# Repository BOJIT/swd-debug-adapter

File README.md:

# swd-debug-adapter

Simple PCB to breakout various debug interfaces used across projects

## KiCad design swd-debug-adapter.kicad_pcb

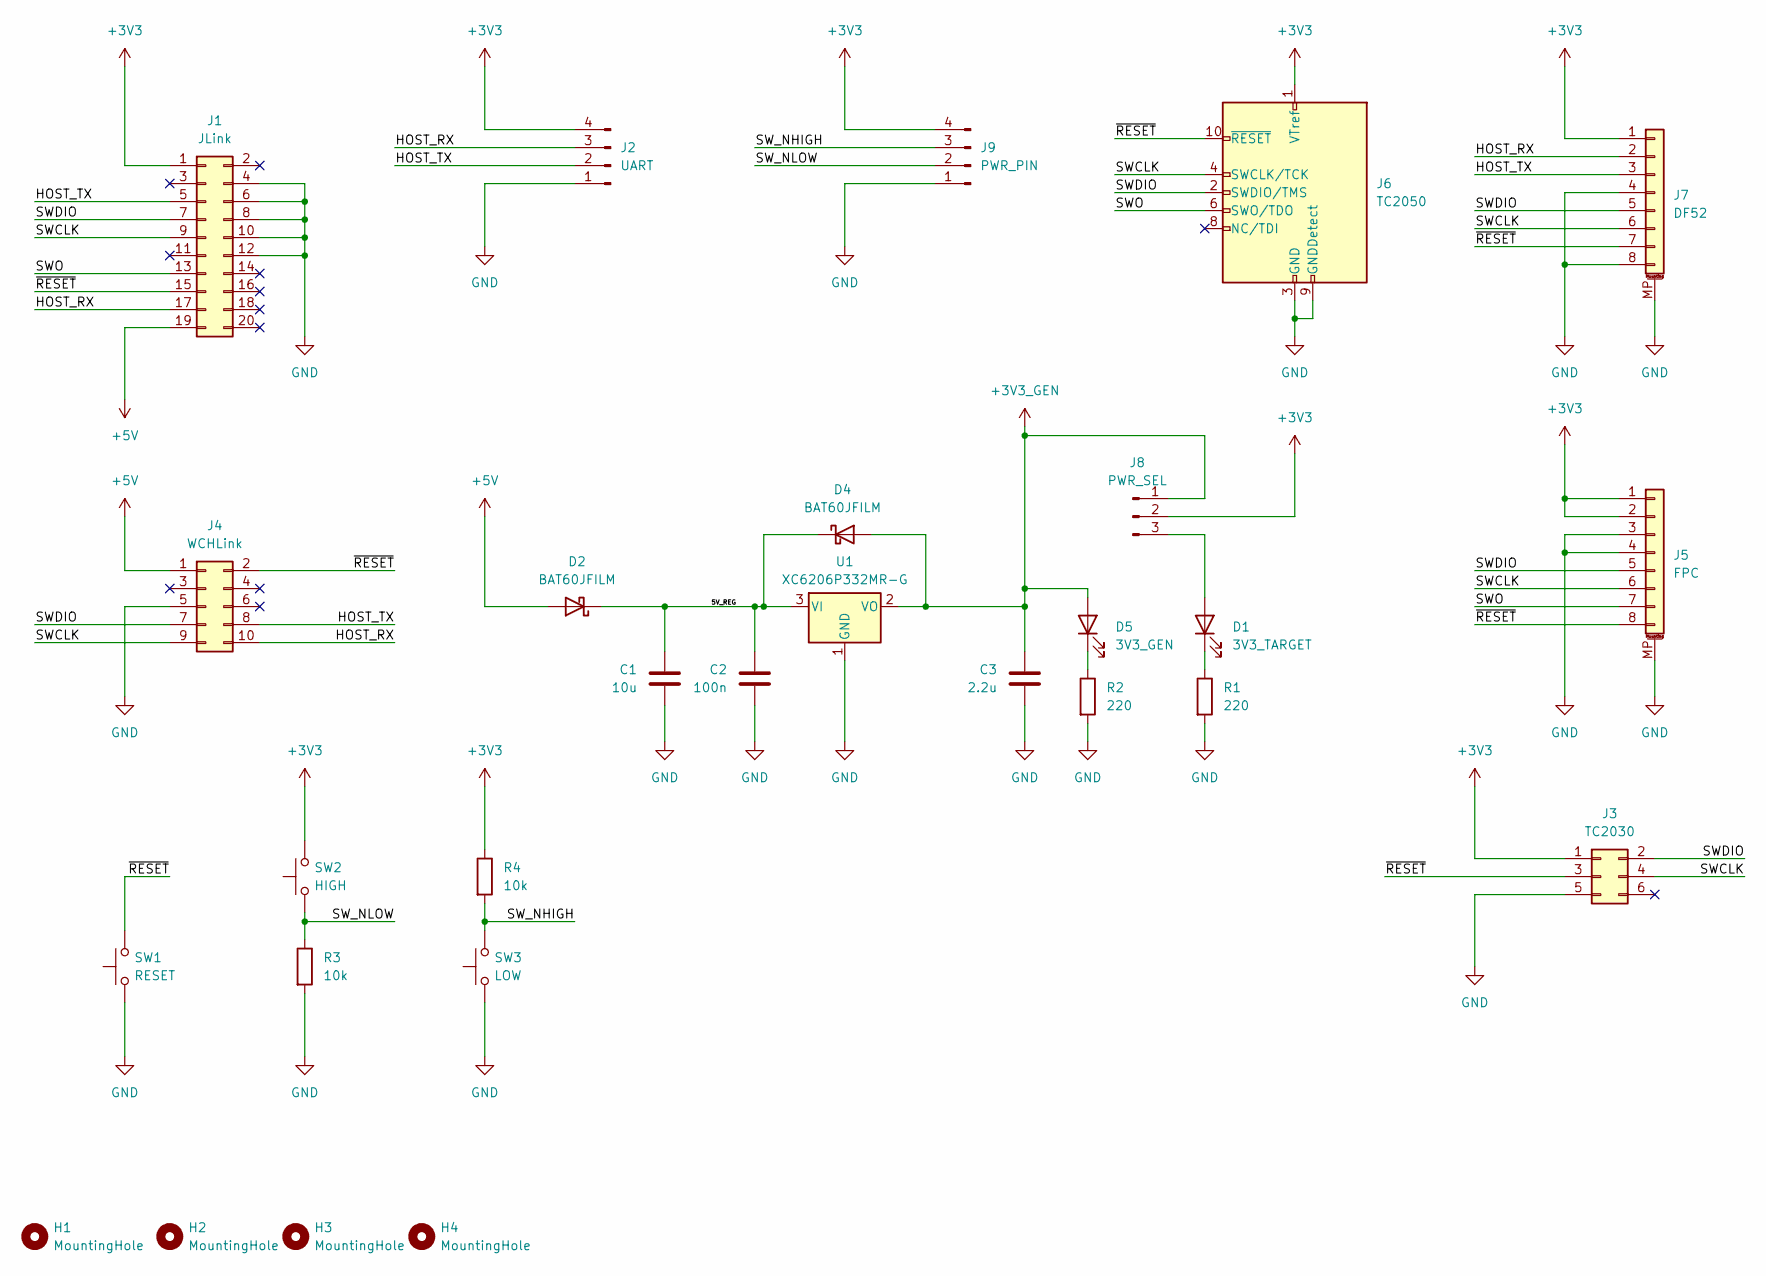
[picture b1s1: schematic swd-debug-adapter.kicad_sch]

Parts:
C1: 10u; C_0603_1608Metric; LCSC Part C19702
C2: 100n; C_0402_1005Metric; LCSC Part C1525
C3: 2.2u; C_0402_1005Metric; LCSC Part C12530
D1: 3V3_TARGET; LED_0603_1608Metric; LCSC Part C2286
D2, D4: BAT60JFILM; D_SOD-323; LCSC Part C133103
D5: 3V3_GEN; LED_0603_1608Metric; LCSC Part C2286
H1, H2, H3, H4: MountingHole; MountingHole_3.2mm_M3_Pad
J1: JLink; IDC-Header_2x10_P2.54mm_Vertical; LCSC Part C3405
J2: UART; PinHeader_1x04_P2.54mm_Vertical
J3: TC2030; CONN-TH_6P-P1.27_HX-JN1.27-2X3P-ZZ-H4.9; LCSC Part C42372545
J4: WCHLink; IDC-Header_2x05_P2.54mm_Vertical; LCSC Part C5665
J5: FPC; Hirose_FH12-8S-0.5SH_1x08-1MP_P0.50mm_Horizontal; LCSC Part C66953
J6: TC2050; CONN-TH_10P-P1.27_HX-JN1.27-2X5P-ZZ-H4.9; LCSC Part C42372547
J7: DF52; Hirose_DF52-8S-0.8H_1x08-1MP_P0.80mm_Horizontal; LCSC Part C506726
J8: PWR_SEL; PinHeader_1x03_P2.54mm_Vertical
J9: PWR_PIN; PinHeader_1x04_P2.54mm_Vertical
R1, R2: 220; R_0402_1005Metric; LCSC Part C25091
R3, R4: 10k; R_0402_1005Metric; LCSC Part C25744
SW1: RESET; SW_Push_1P1T_XKB_TS-1187A; LCSC Part C318884
SW2: HIGH; SW_Push_1P1T_XKB_TS-1187A; LCSC Part C318884
SW3: LOW; SW_Push_1P1T_XKB_TS-1187A; LCSC Part C318884
U1: XC6206P332MR-G; SOT-23-3; LCSC Part C5446

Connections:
+3V3: J1.1, J2.4, J3.1, J5.1, J5.2, J6.1 (VTref), J7.1, J8.2, J9.4, R4.1, SW2.2
+3V3_GEN: C3.1, D4.2 (A), D5.2 (A), J8.1, U1.2 (VO)
+5V: D2.2 (A), J1.19, J4.1
/5V_REG: C1.1, C2.1, D2.1 (K), D4.1 (K), U1.3 (VI)
/HOST_RX: J1.17, J2.3, J4.10, J7.2
/HOST_TX: J1.5, J2.2, J4.8, J7.3
/SWCLK: J1.9, J3.4, J4.9, J5.6, J6.4 (SWCLK/TCK), J7.6
/SWDIO: J1.7, J3.2, J4.7, J5.5, J6.2 (SWDIO/TMS), J7.5
/SWO: J1.13, J5.7, J6.6 (SWO/TDO)
/SW_NHIGH: J9.3, R4.2, SW3.2
/SW_NLOW: J9.2, R3.1, SW2.1
/~RESET: J1.15, J3.3, J4.2, J5.8, J6.10 (~RESET), J7.7, SW1.2
GND: C1.2, C2.2, C3.2, J1.4, J1.6, J1.8, J1.10, J1.12, J2.1, J3.5, J4.5, J5.3, J5.4, J5.MP (MountPin), J6.3 (GND), J6.5 (GND), J6.9 (GNDDetect), J7.4, J7.8, J7.MP (MountPin), J9.1, R1.2, R2.2, R3.2, SW1.1, SW3.1, U1.1 (GND)
unnamed: D1.2 (A), J8.3
unnamed: D1.1 (K), R1.1
unnamed: D5.1 (K), R2.1

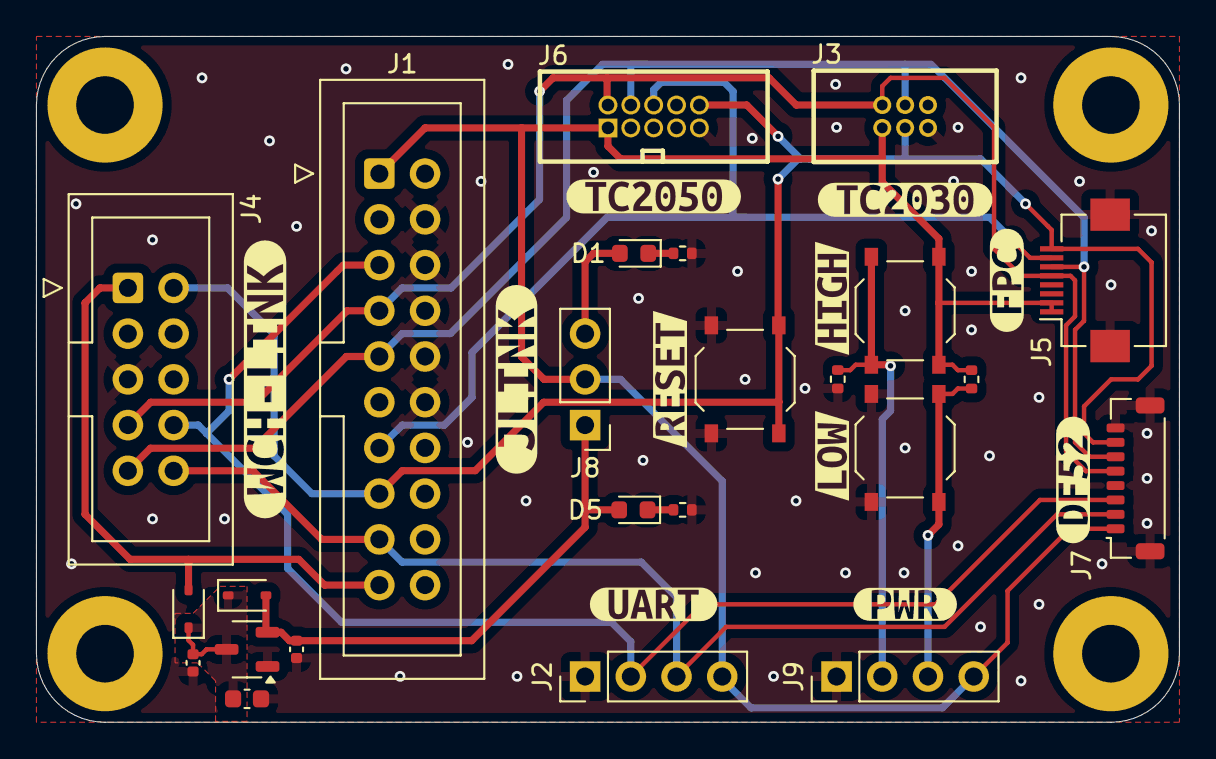
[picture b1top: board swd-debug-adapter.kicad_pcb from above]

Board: 2 copper layers, 63.5 x 38.1 mm, 39 parts (0 on the bottom side), 16 nets.

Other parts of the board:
kibuzzard-695AA98E: G***; kibuzzard-695AA98E
kibuzzard-695AAA64: G***; kibuzzard-695AAA64
kibuzzard-695AAA74: G***; kibuzzard-695AAA74
kibuzzard-695ABB1F: G***; kibuzzard-695ABB1F
kibuzzard-695ABBBA: G***; kibuzzard-695ABBBA
kibuzzard-695ABBC6: G***; kibuzzard-695ABBC6
kibuzzard-695ABEB9: G***; kibuzzard-695ABEB9
kibuzzard-695ABEC3: G***; kibuzzard-695ABEC3
kibuzzard-695ABECD: G***; kibuzzard-695ABECD
kibuzzard-695ABEEB: G***; kibuzzard-695ABEEB
kibuzzard-695ABEF1: G***; kibuzzard-695ABEF1

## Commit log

2026-01-04 Schematics done
2026-01-04 Part export
2026-01-04 Fix prod files
